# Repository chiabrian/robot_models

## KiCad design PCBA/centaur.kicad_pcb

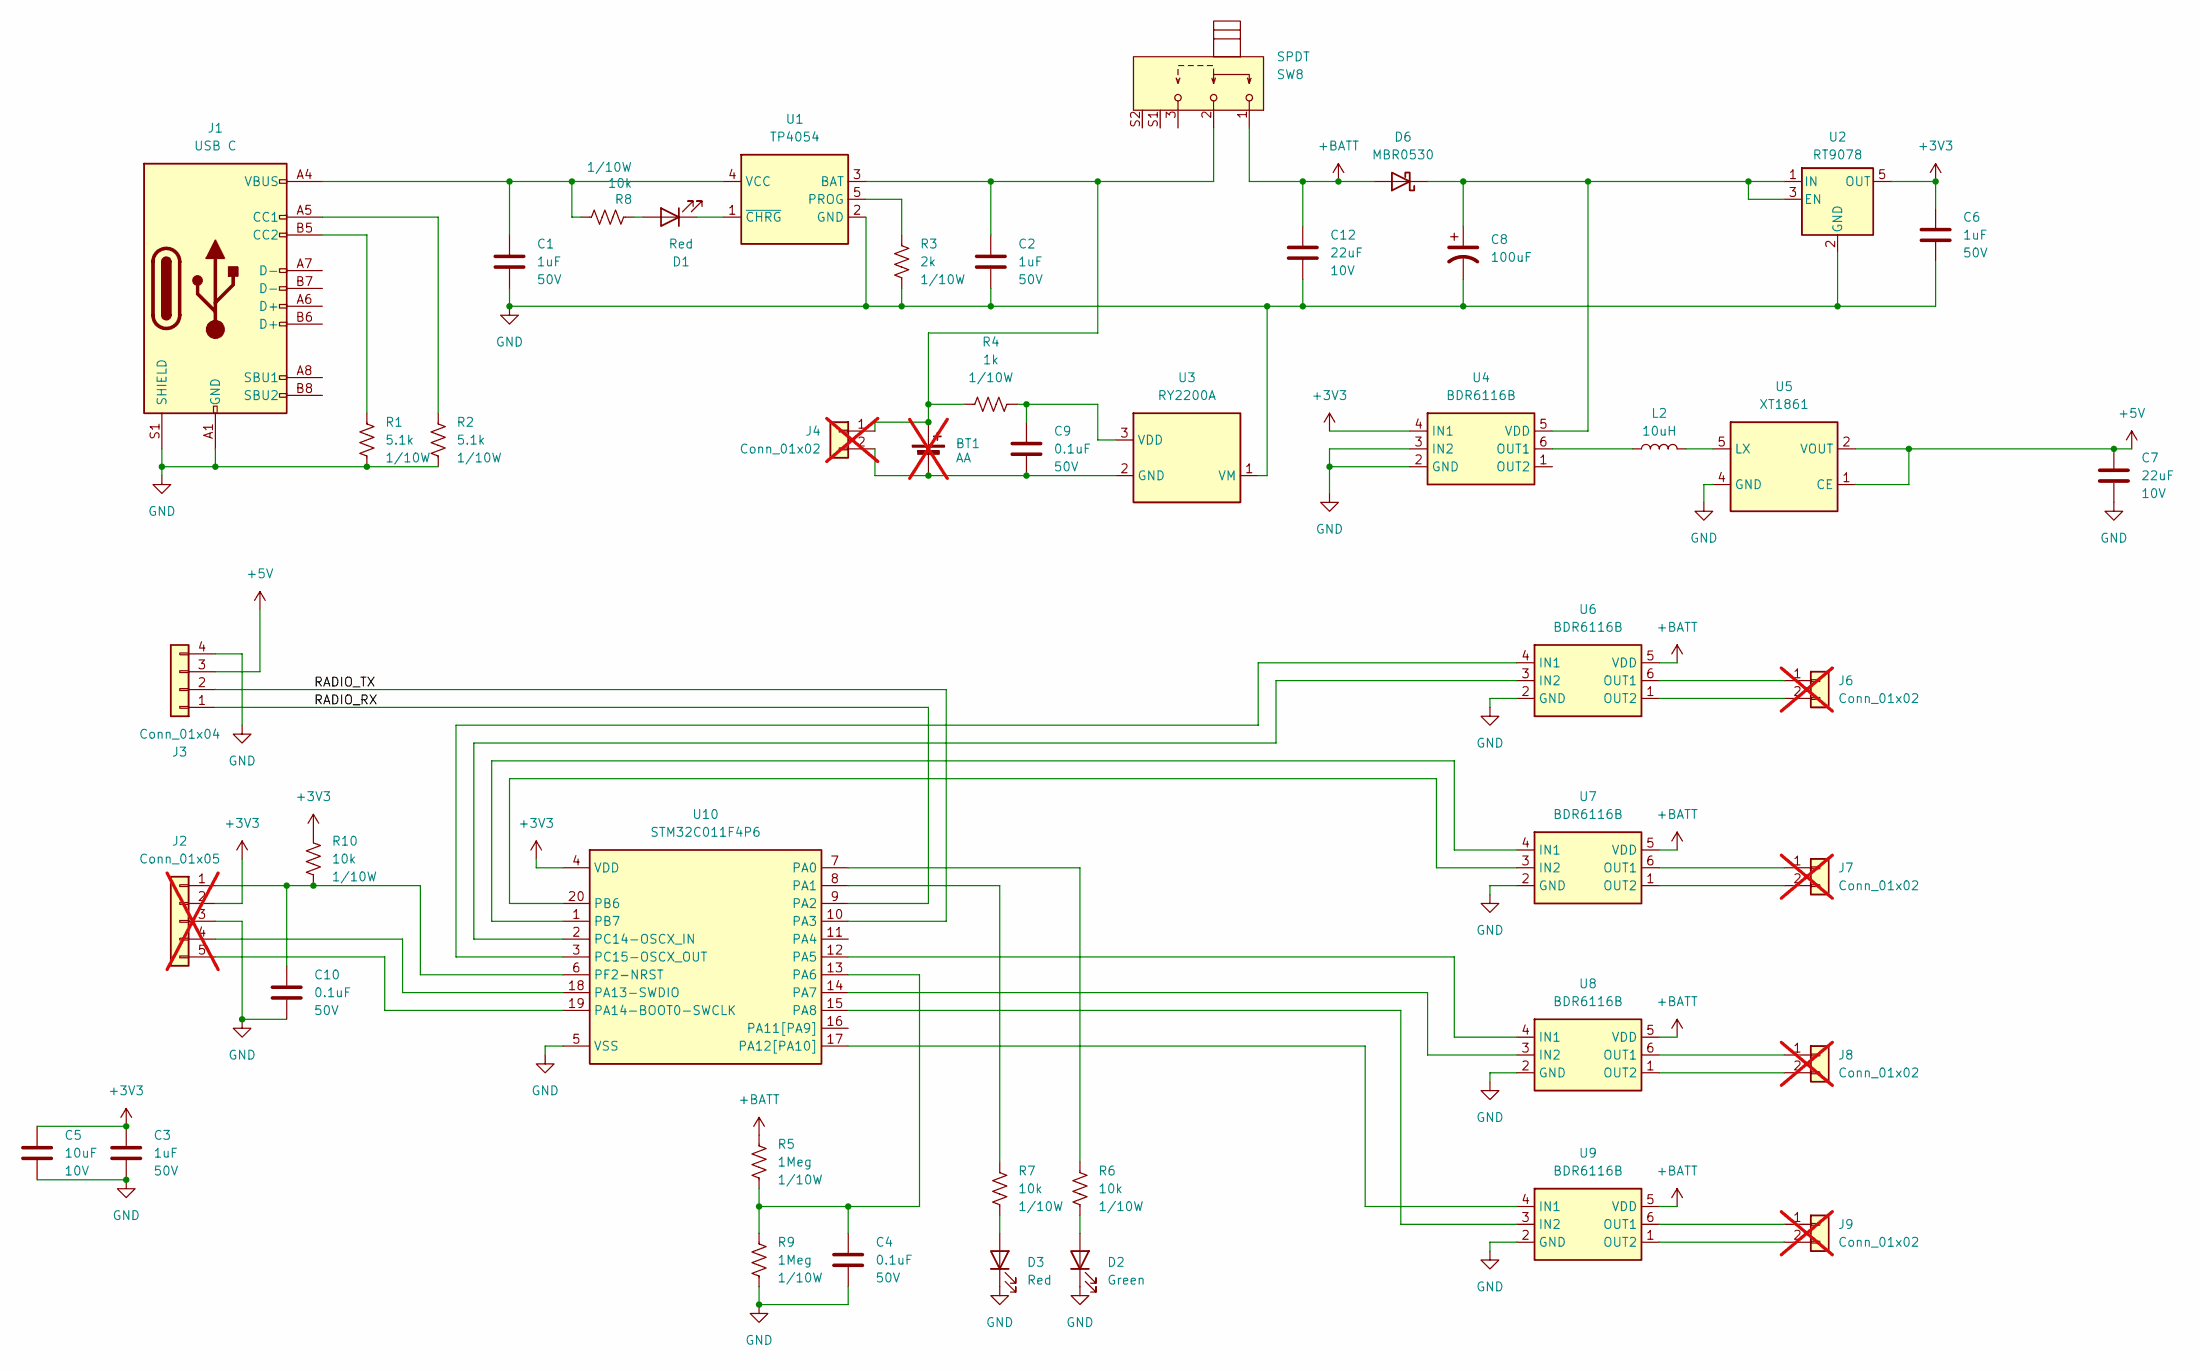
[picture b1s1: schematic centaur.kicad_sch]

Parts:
BT1: AA; Battery_Holder_MPD_BCAAPC; Manufacturer Part Numbe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 2460; LCSC Part Number C5370863; not fitted
C1, C2, C3, C6: 1uF; C_0603_1608Metric; Voltage 50V; Tolerance 10%; Manufacturer Part Numbe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 CL10A105KB8NNNC; LCSC Part Number C15849
C4, C9, C10: 0.1uF; C_0603_1608Metric; Voltage 50V; Tolerance 10%; Manufacturer Part Numbe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 CL10B104KB8NNNC; LCSC Part Number C14663
C5: 10uF; C_0603_1608Metric; Voltage 10V; Tolerance 10%; Manufacturer Part Numbe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 CL10A106KP8NNNC; LCSC Part Number C19702
C7, C12: 22uF; C_0603_1608Metric; Voltage 10V; Tolerance 20%; Manufacturer Part Numbe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 CL10A226MP8NUNE; LCSC Part Number C86295
C8: 100uF; CP_Radial_D6.3mm_P2.50mm_H11mm_H2
D1, D3: Red; LED_0603_1608Metric_Pad1.05x0.95mm_HandSolder; Manufacturer Part Numbe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 KT-0603R; LCSC Part Number C2286
D2: Green; LED_0603_1608Metric_Pad1.05x0.95mm_HandSolder; Manufacturer Part Numbe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 KT-0603G; LCSC Part Number C12624
D6: MBR0530; D_SOD-123; Manufacturer Part Numbe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 MBR0530; LCSC Part Number C22378361
J1: USB C; USBC_16P; Voltage 20V; Manufacturer Part Numbe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 HC-TYPE-C-16P-01A; LCSC Part Number C2894897
J2: Conn_01x05; PinHeader_1x05_P2.54mm_Vertical; not fitted
J3: Conn_01x04; PinSocket_1x04_P2.54mm_Horizontal
J4, J6, J7, J8, J9: Conn_01x02; PinHeader_1x02_P2.54mm_Vertical; not fitted
L2: 10uH; L_4.5x4.0_H3.2; Tolerance 20%; Manufacturer Part Numbe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 CD43-100M; LCSC Part Number C18734467
R1, R2: 5.1k; R_0603_1608Metric_Pad0.98x0.95mm_HandSolder; Tolerance 1%; Manufacturer Part Numbe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 RC0603FR-075K1L; LCSC Part Number C23186
R3: 2k; R_0603_1608Metric_Pad0.98x0.95mm_HandSolder; Tolerance 1%; Manufacturer Part Numbe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 RC0603FR-072K1L; LCSC Part Number C163892
R4: 1k; R_0603_1608Metric_Pad0.98x0.95mm_HandSolder; Tolerance 1%; Manufacturer Part Numbe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 RC0603FR-071KL; LCSC Part Number C21190
R5, R9: 1Meg; R_0603_1608Metric_Pad0.98x0.95mm_HandSolder; Tolerance 1%; Manufacturer Part Numbe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 RC0603FR-071ML
R6, R7, R8, R10: 10k; R_0603_1608Metric_Pad0.98x0.95mm_HandSolder; Tolerance 1%; Manufacturer Part Numbe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 RC0603FR-0710KL; LCSC Part Number C25804
SW8: SPDT; SW_SPDT_Slide_CK_SK12D07VG4; Voltage 30V; Manufacturer Part Numbe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 SK12D07VG4; LCSC Part Number C22435621
U1: TP4054; SOT-23-5; Voltage 4.2-6.5V; Manufacturer Part Numbe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 TP4054; LCSC Part Number C668215
U2: RT9078; SOT-23-5; Voltage 1.2-5.5V; Manufacturer Part Numbe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 RT9078-33GJ5; LCSC Part Number C110427
U3: RY2200A; SOT-23-3; Voltage 6V; Manufacturer Part Numbe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 RY2200At3; LCSC Part Number C48580216
U4, U6, U7, U8, U9: BDR6116B; SOT-23-6; Voltage 2-6.5V; Manufacturer Part Numbe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 BDR6116B; LCSC Part Number C52200573
U5: XT1861; SOT-23-5; Voltage 1.8-5V; Manufacturer Part Numbe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 XT1861B502SR-G; LCSC Part Number C3008013
U10: STM32C011F4P6; TSSOP-20_4.4x6.5mm_P0.65mm; Voltage 2-3.6V; Manufacturer Part Numbe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 STM32C011F4P6; LCSC Part Number C7373263

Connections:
+3V3: C3.1, C5.1, C6.1, J2.2, R10.1, U2.5 (OUT), U4.4 (IN1), U10.4 (VDD)
+5V: C7.1, J3.3, U5.1 (CE), U5.2 (VOUT)
+BATT: C12.1, D6.2 (A), R5.1, SW8.1, U6.5 (VDD), U7.5 (VDD), U8.5 (VDD), U9.5 (VDD)
/RADIO_RX: J3.1, U10.9 (PA2)
/RADIO_TX: J3.2, U10.10 (PA3)
GND: C1.2, C2.2, C3.2, C4.2, C5.2, C6.2, C7.2, C8.2, C10.2, C12.2, D2.1 (K), D3.1 (K), J1.A1 (GND), J1.A12 (GND), J1.B1 (GND), J1.B12 (GND), J1.S1 (SHIELD), J2.3, J3.4, R1.2, R2.2, R3.2, R9.2, U1.2 (GND), U2.2 (GND), U3.1 (VM), U4.2 (GND), U4.3 (IN2), U5.4 (GND), U6.2 (GND), U7.2 (GND), U8.2 (GND), U9.2 (GND), U10.5 (VSS)
unnamed: BT1.1 (+), C2.1, J4.1, R4.1, SW8.2, U1.3 (BAT)
unnamed: BT1.2 (-), C9.2, J4.2, U3.2 (GND)
unnamed: D1.2 (A), R8.1
unnamed: D1.1 (K), U1.1 (~CHRG)
unnamed: D2.2 (A), R6.2
unnamed: D3.2 (A), R7.2
unnamed: C8.1, D6.1 (K), U2.1 (IN), U2.3 (EN), U4.5 (VDD)
unnamed: J1.A5 (CC1), R2.1
unnamed: J1.B5 (CC2), R1.1
unnamed: C10.1, J2.1, R10.2, U10.6 (PF2-NRST)
unnamed: J2.4, U10.18 (PA13-SWDIO)
unnamed: J2.5, U10.19 (PA14-BOOT0-SWCLK)
unnamed: J6.1, U6.6 (OUT1)
unnamed: J6.2, U6.1 (OUT2)
unnamed: J7.1, U7.6 (OUT1)
unnamed: J7.2, U7.1 (OUT2)
unnamed: J8.1, U8.6 (OUT1)
unnamed: J8.2, U8.1 (OUT2)
unnamed: J9.1, U9.6 (OUT1)
unnamed: J9.2, U9.1 (OUT2)
unnamed: R3.1, U1.5 (PROG)
unnamed: C1.1, J1.A4 (VBUS), J1.A9 (VBUS), J1.B4 (VBUS), J1.B9 (VBUS), R8.2, U1.4 (VCC)
unnamed: C9.1, R4.2, U3.3 (VDD)
unnamed: L2.1, U4.6 (OUT1)
unnamed: L2.2, U5.5 (LX)
unnamed: R6.1, U10.7 (PA0)
unnamed: R7.1, U10.8 (PA1)
unnamed: U8.4 (IN1), U10.12 (PA5)
unnamed: C4.1, R5.2, R9.1, U10.13 (PA6)
unnamed: U8.3 (IN2), U10.14 (PA7)
unnamed: U9.3 (IN2), U10.15 (PA8)
unnamed: U9.4 (IN1), U10.17 (PA12[PA10])
unnamed: U7.3 (IN2), U10.20 (PB6)
unnamed: U7.4 (IN1), U10.1 (PB7)
unnamed: U6.3 (IN2), U10.2 (PC14-OSCX_IN)
unnamed: U6.4 (IN1), U10.3 (PC15-OSCX_OUT)

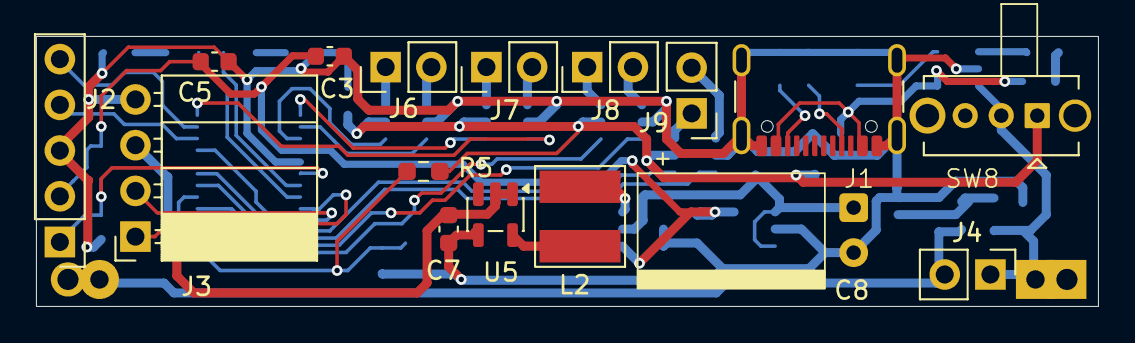
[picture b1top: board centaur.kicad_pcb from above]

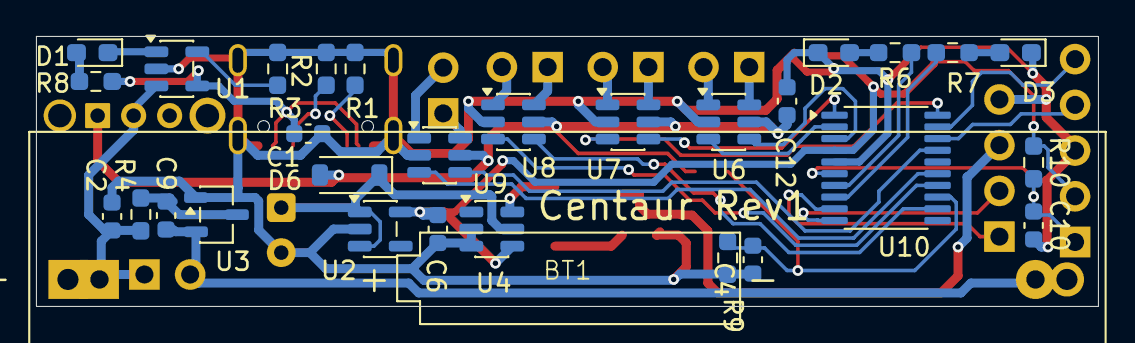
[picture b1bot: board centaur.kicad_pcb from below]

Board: 2 copper layers, 59.0 x 15.0 mm, 46 parts (30 on the bottom side), 42 nets.

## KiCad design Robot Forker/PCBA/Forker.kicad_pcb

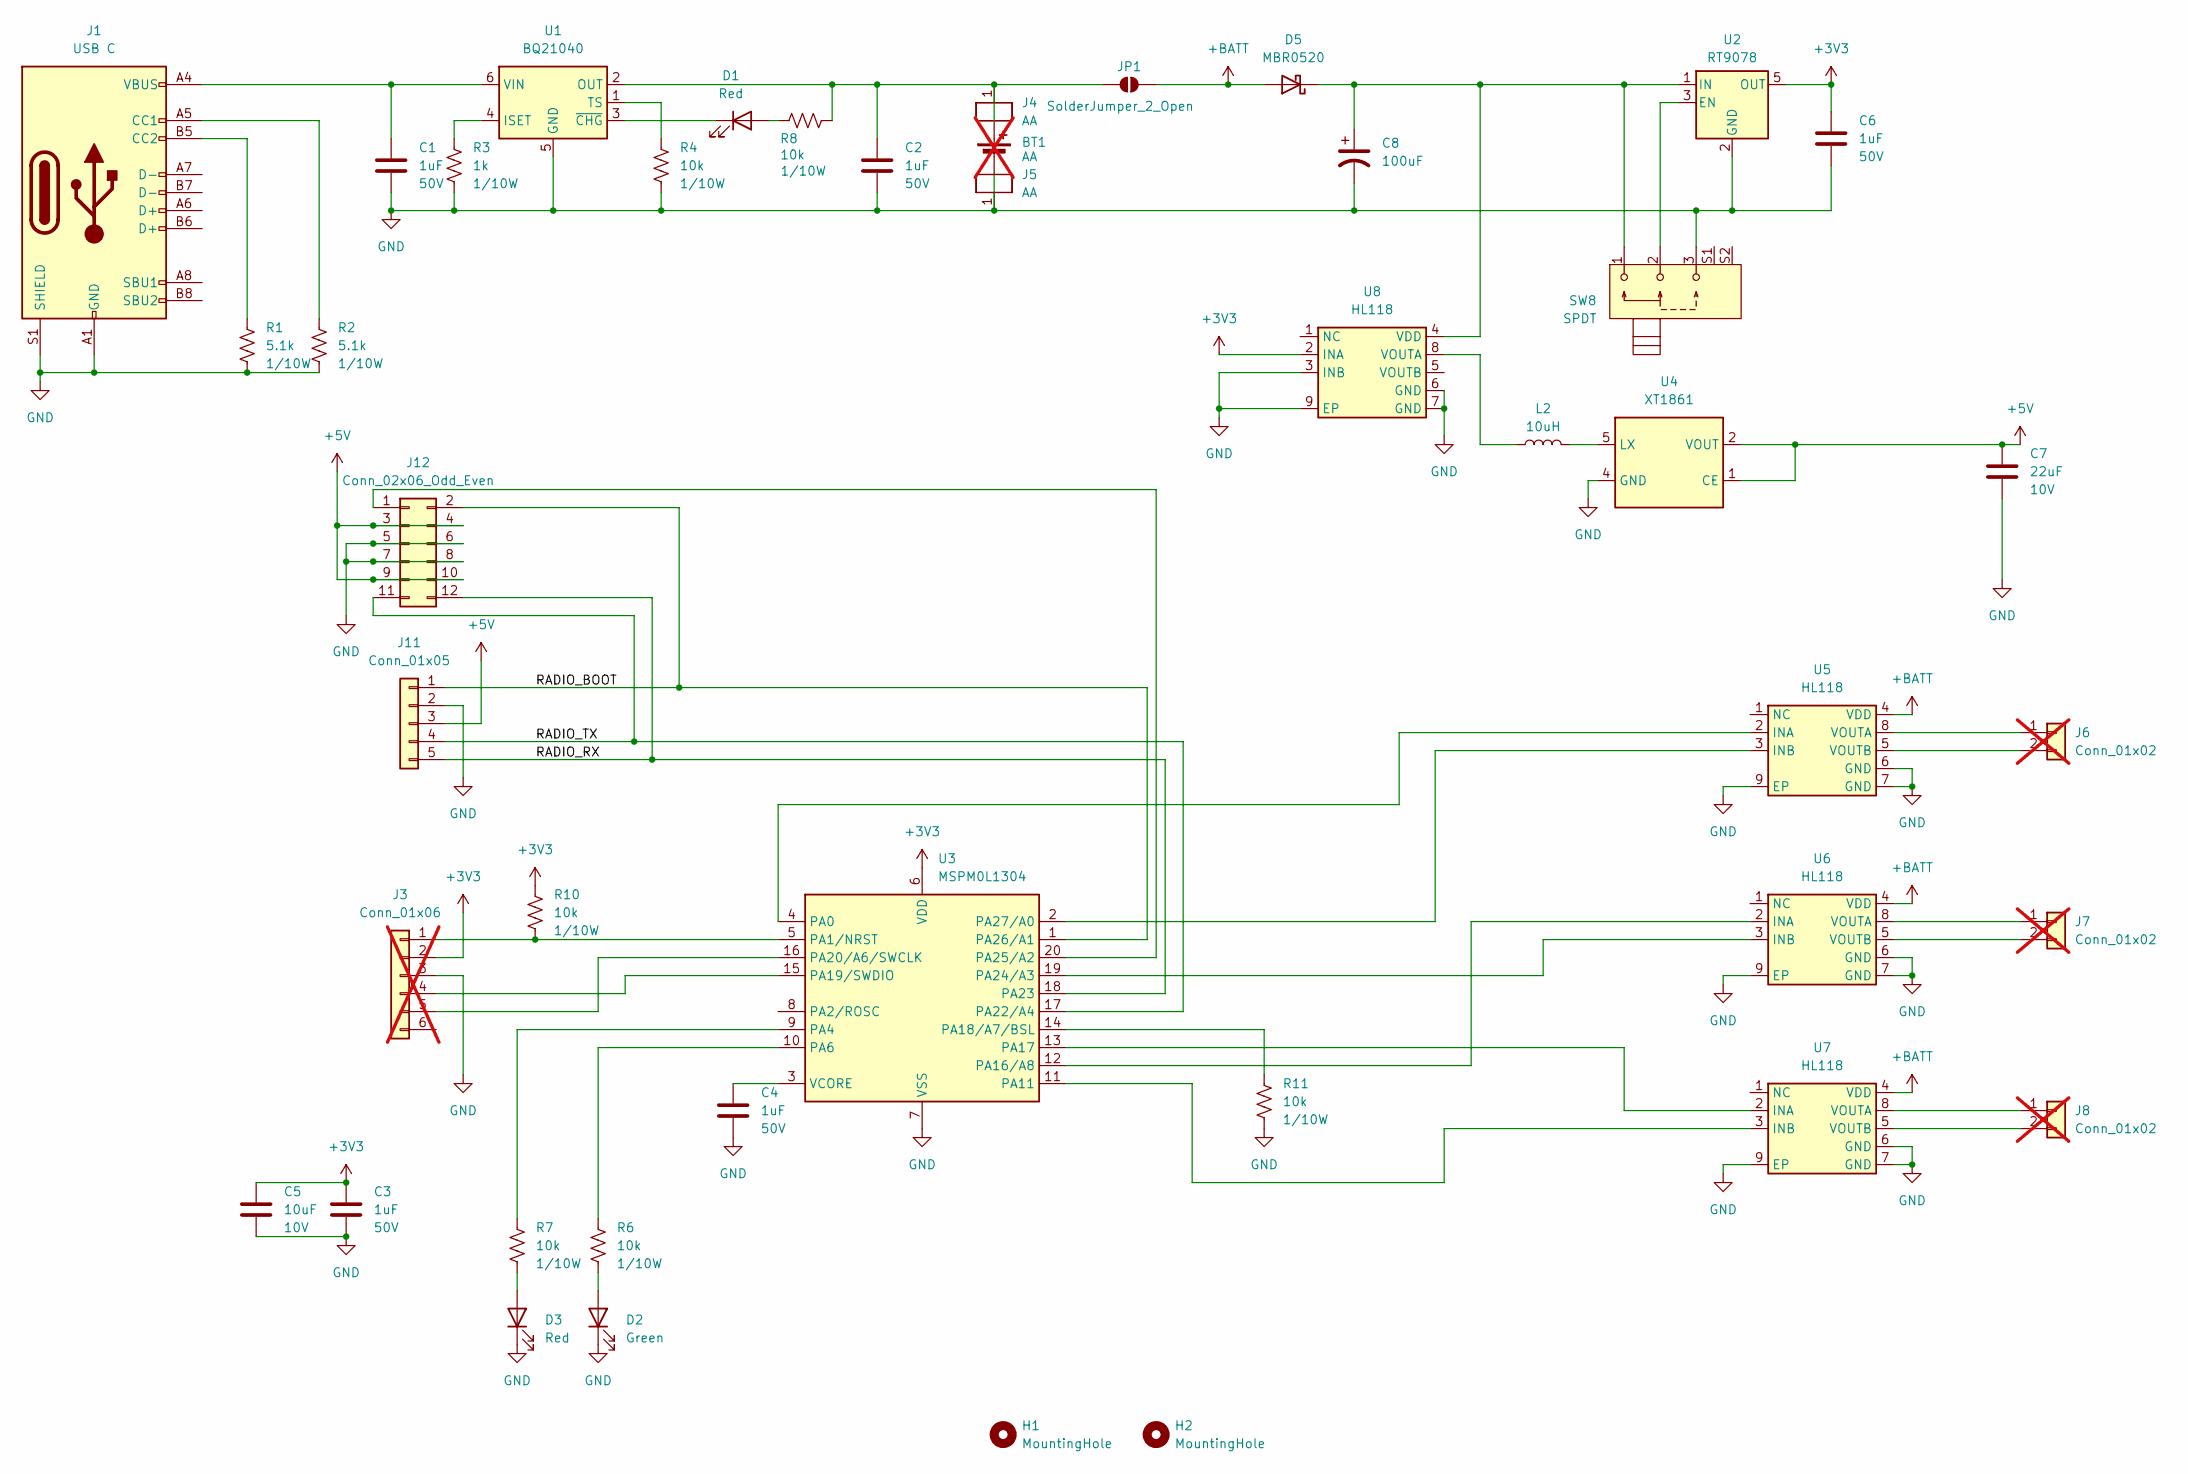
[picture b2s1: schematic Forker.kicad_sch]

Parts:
BT1: AA; Battery_Holder_MPD_BCAAPC; Manufacturer Part Numbe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 2460; LCSC Part Number C5370863; not fitted
C1, C2, C3, C4, C6: 1uF; C_0603_1608Metric; Voltage 50V; Tolerance 10%; Manufacturer Part Numbe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 CL10A105KB8NNNC; LCSC Part Number C15849
C5: 10uF; C_0603_1608Metric; Voltage 10V; Tolerance 10%; Manufacturer Part Numbe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 CL10A106KP8NNNC; LCSC Part Number C19702
C7: 22uF; C_0603_1608Metric; Voltage 10V; Tolerance 20%; Manufacturer Part Numbe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 CL10A226MP8NUNE; LCSC Part Number C86295
C8: 100uF; CP_Radial_D6.3mm_P2.50mm
D1, D3: Red; LED_0603_1608Metric_Pad1.05x0.95mm_HandSolder; Manufacturer Part Numbe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 KT-0603R; LCSC Part Number C2286
D2: Green; LED_0603_1608Metric_Pad1.05x0.95mm_HandSolder; Manufacturer Part Numbe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 KT-0603G; LCSC Part Number C12624
D5: MBR0520; D_SOD-123
H1, H2: MountingHole; MountingHole_2.2mm_M2
J1: USB C; USBC_16P; Voltage 20V; Manufacturer Part Numbe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 HC-TYPE-C-16P-01A; LCSC Part Number C2894897
J3: Conn_01x06; PinHeader_1x06_P2.54mm_Vertical; not fitted
J4, J5: AA; Battery_Clip_Keystone_53; Manufacturer Part Numbe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 53; LCSC Part Number C5352788
J6, J7, J8: Conn_01x02; PinHeader_1x02_P2.54mm_Vertical; not fitted
J11: Conn_01x05; PinHeader_1x05_P2.54mm_Horizontal
J12: Conn_02x06_Odd_Even; PinHeader_2x06_P2.54mm_Horizontal
JP1: SolderJumper_2_Open; SolderJumper-2_P1.3mm_Open_TrianglePad1.0x1.5mm
L2: 10uH; L_4.5x4.0_H3.2; Tolerance 20%; Manufacturer Part Numbe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 CD43-100M; LCSC Part Number C18734467
R1, R2: 5.1k; R_0603_1608Metric_Pad0.98x0.95mm_HandSolder; Tolerance 1%; Manufacturer Part Numbe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 RC0603FR-075K1L; LCSC Part Number C23186
R3: 1k; R_0603_1608Metric_Pad0.98x0.95mm_HandSolder; Tolerance 1%; Manufacturer Part Numbe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 RC0603FR-071KL; LCSC Part Number C21190
R4, R6, R7, R8, R10, R11: 10k; R_0603_1608Metric_Pad0.98x0.95mm_HandSolder; Tolerance 1%; Manufacturer Part Numbe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 RC0603FR-0710KL; LCSC Part Number C25804
SW8: SPDT; SW_SPDT_Slide_CK_SK12D07VG4; Voltage 30V; Manufacturer Part Numbe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 SK12D07VG4; LCSC Part Number C22435621
U1: BQ21040; SOT-23-6; Voltage 3.5-28V; Manufacturer Part Numbe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 BQ21040DBVR; LCSC Part Number C202311
U2: RT9078; SOT-23-5; Voltage 1.2-5.5V; Manufacturer Part Numbe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 RT9078-33GJ5; LCSC Part Number C110427
U3: MSPM0L1304; TI_DGS20; Voltage 1.62-3.6V; Manufacturer Part Numbe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 MSPM0L1304TDGS20R; LCSC Part Number C22362611
U4: XT1861; SOT-23-5; Voltage 1.8-5V; Manufacturer Part Numbe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 XT1861B502SR-G; LCSC Part Number C3008013
U5, U6, U7, U8: HL118; SOP-8-1EP_3.9x4.9mm_P1.27mm_EP2.4x3.3mm; Voltage 1.8-8.5V; Manufacturer Part Numbe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 HL118; LCSC Part Number C42372074

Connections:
+3V3: C3.1, C5.1, C6.1, J3.2, R10.1, U2.5 (OUT), U3.6 (VDD), U8.2 (INA)
+5V: C7.1, J11.3, J12.3, J12.4, J12.9, J12.10, U4.1 (CE), U4.2 (VOUT)
+BATT: D5.2 (A), JP1.2 (B), U5.4 (VDD), U6.4 (VDD), U7.4 (VDD)
/RADIO_BOOT: J11.1, J12.2, U3.1 (PA26/A1)
/RADIO_RX: J11.5, J12.12, U3.18 (PA23)
/RADIO_TX: J11.4, J12.11, U3.17 (PA22/A4)
GND: BT1.2 (-), C1.2, C2.2, C3.2, C4.2, C5.2, C6.2, C7.2, C8.2, D2.1 (K), D3.1 (K), J1.A1 (GND), J1.A12 (GND), J1.B1 (GND), J1.B12 (GND), J1.S1 (SHIELD), J3.3, J5.1, J11.2, J12.5, J12.6, J12.7, J12.8, R1.2, R2.2, R3.2, R4.1, R11.2, SW8.3, U1.5 (GND), U2.2 (GND), U3.7 (VSS), U4.4 (GND), U5.6 (GND), U5.7 (GND), U5.9 (EP), U6.6 (GND), U6.7 (GND), U6.9 (EP), U7.6 (GND), U7.7 (GND), U7.9 (EP), U8.3 (INB), U8.6 (GND), U8.7 (GND), U8.9 (EP)
unnamed: BT1.1 (+), C2.1, J4.1, JP1.1 (A), R8.2, U1.2 (OUT)
unnamed: D1.2 (A), R8.1
unnamed: D1.1 (K), U1.3 (~CHG)
unnamed: D2.2 (A), R6.2
unnamed: D3.2 (A), R7.2
unnamed: C8.1, D5.1 (K), SW8.1, U2.1 (IN), U8.4 (VDD)
unnamed: J1.A5 (CC1), R2.1
unnamed: J1.B5 (CC2), R1.1
unnamed: J3.1, R10.2, U3.5 (PA1/NRST)
unnamed: J3.4, U3.15 (PA19/SWDIO)
unnamed: J3.5, U3.16 (PA20/A6/SWCLK)
unnamed: J6.1, U5.8 (VOUTA)
unnamed: J6.2, U5.5 (VOUTB)
unnamed: J7.1, U6.8 (VOUTA)
unnamed: J7.2, U6.5 (VOUTB)
unnamed: J8.1, U7.8 (VOUTA)
unnamed: J8.2, U7.5 (VOUTB)
unnamed: J12.1, U3.20 (PA25/A2)
unnamed: R3.1, U1.4 (ISET)
unnamed: R4.2, U1.1 (TS)
unnamed: C1.1, J1.A4 (VBUS), J1.A9 (VBUS), J1.B4 (VBUS), J1.B9 (VBUS), U1.6 (VIN)
unnamed: SW8.2, U2.3 (EN)
unnamed: U3.4 (PA0), U5.2 (INA)
unnamed: R7.1, U3.9 (PA4)
unnamed: R6.1, U3.10 (PA6)
unnamed: U3.11 (PA11), U7.3 (INB)
unnamed: U3.12 (PA16/A8), U6.2 (INA)
unnamed: U3.13 (PA17), U7.2 (INA)
unnamed: R11.1, U3.14 (PA18/A7/BSL)
unnamed: U3.19 (PA24/A3), U6.3 (INB)
unnamed: U3.2 (PA27/A0), U5.3 (INB)
unnamed: C4.1, U3.3 (VCORE)
unnamed: L2.2, U4.5 (LX)
unnamed: L2.1, U8.8 (VOUTA)

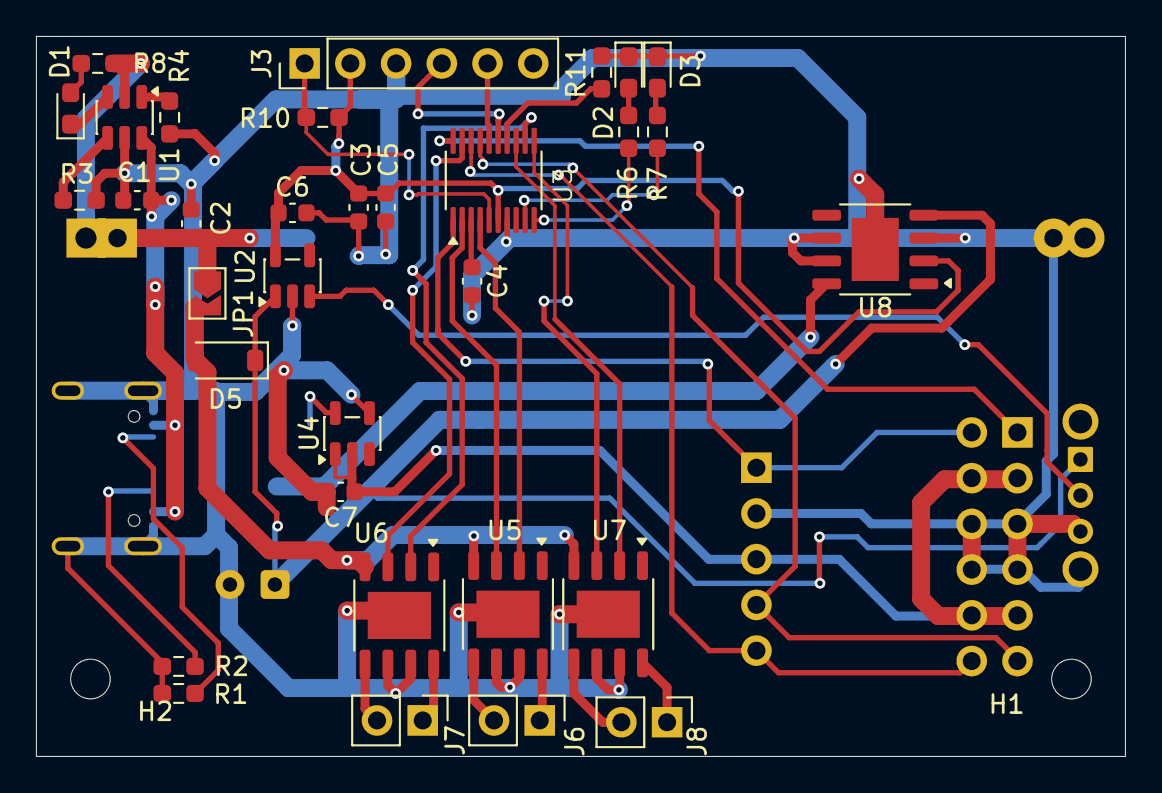
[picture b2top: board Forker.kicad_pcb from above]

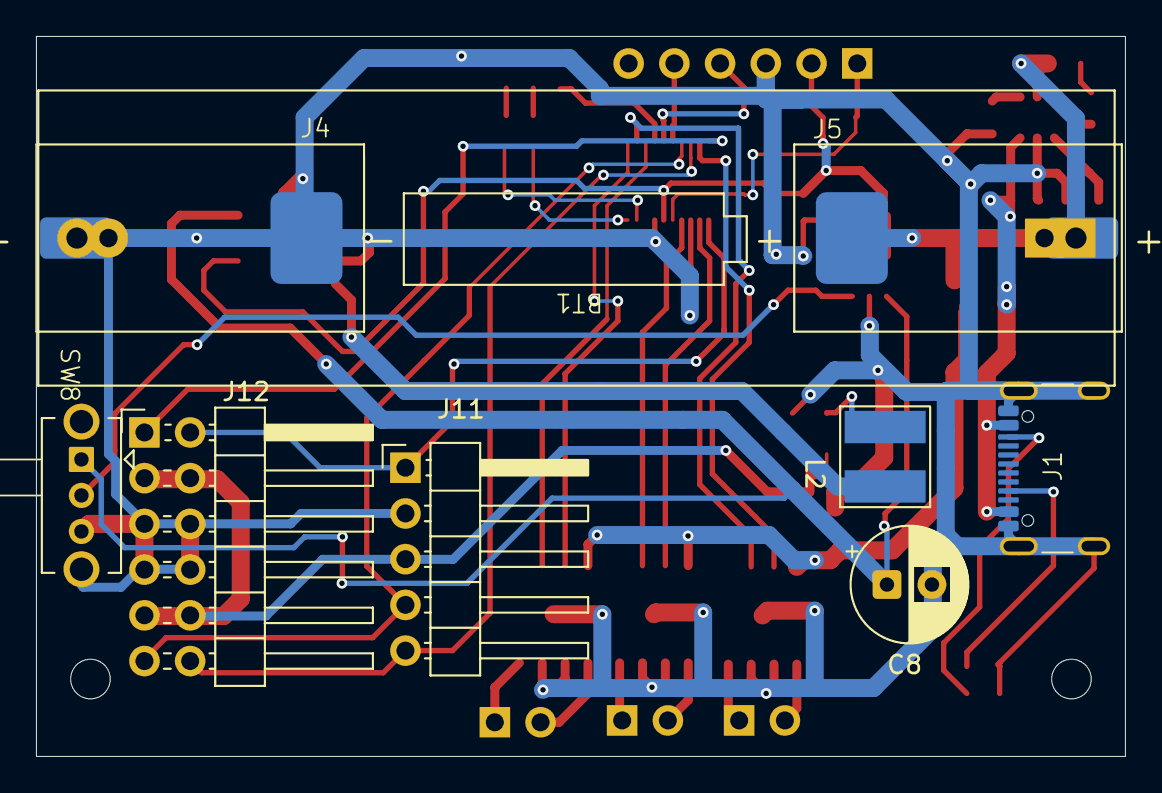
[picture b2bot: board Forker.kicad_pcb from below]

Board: 2 copper layers, 60.5 x 40.0 mm, 44 parts (9 on the bottom side), 41 nets.

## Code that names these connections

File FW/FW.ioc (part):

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Mcu.Name=STM32C011F(4-6)Px
Mcu.Package=TSSOP20
Mcu.UserName=STM32C011F4Px
PA0.Signal=GPIO_Output
PA1.Signal=GPIO_Output
PA13.Mode=Serial_Wire
PA13.Signal=DEBUG_SWDIO
PA14-BOOT0.Mode=Serial_Wire
PA14-BOOT0.Signal=DEBUG_SWCLK
PA2.Mode=Asynchronous
PA2.Signal=USART2_TX
PA3.Mode=Asynchronous
PA3.Signal=USART2_RX
PA5.Mode=PWM Generation3 CH3N
PA5.Signal=TIM1_CH3N
PA6.Mode=IN6
PA6.Signal=ADC1_IN6
PA7.Mode=PWM Generation1 CH1N
PA7.Signal=TIM1_CH1N
PB6.Signal=S_TIM3_CH1
PB7.Signal=S_TIM3_CH4
PC14-OSCX_IN\ (PC14).Signal=S_TIM3_CH2
PC15-OSCX_OUT\ (PC15).Signal=S_TIM3_CH3
PF2-NRST.Signal=S_TIM1_CH4
RCC.HSE_VALUE=8000000
RCC.SYSCLKFreq_VALUE=48000000
board=custom

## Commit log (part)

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2026-06-26 Increase axle size for FDM printer
